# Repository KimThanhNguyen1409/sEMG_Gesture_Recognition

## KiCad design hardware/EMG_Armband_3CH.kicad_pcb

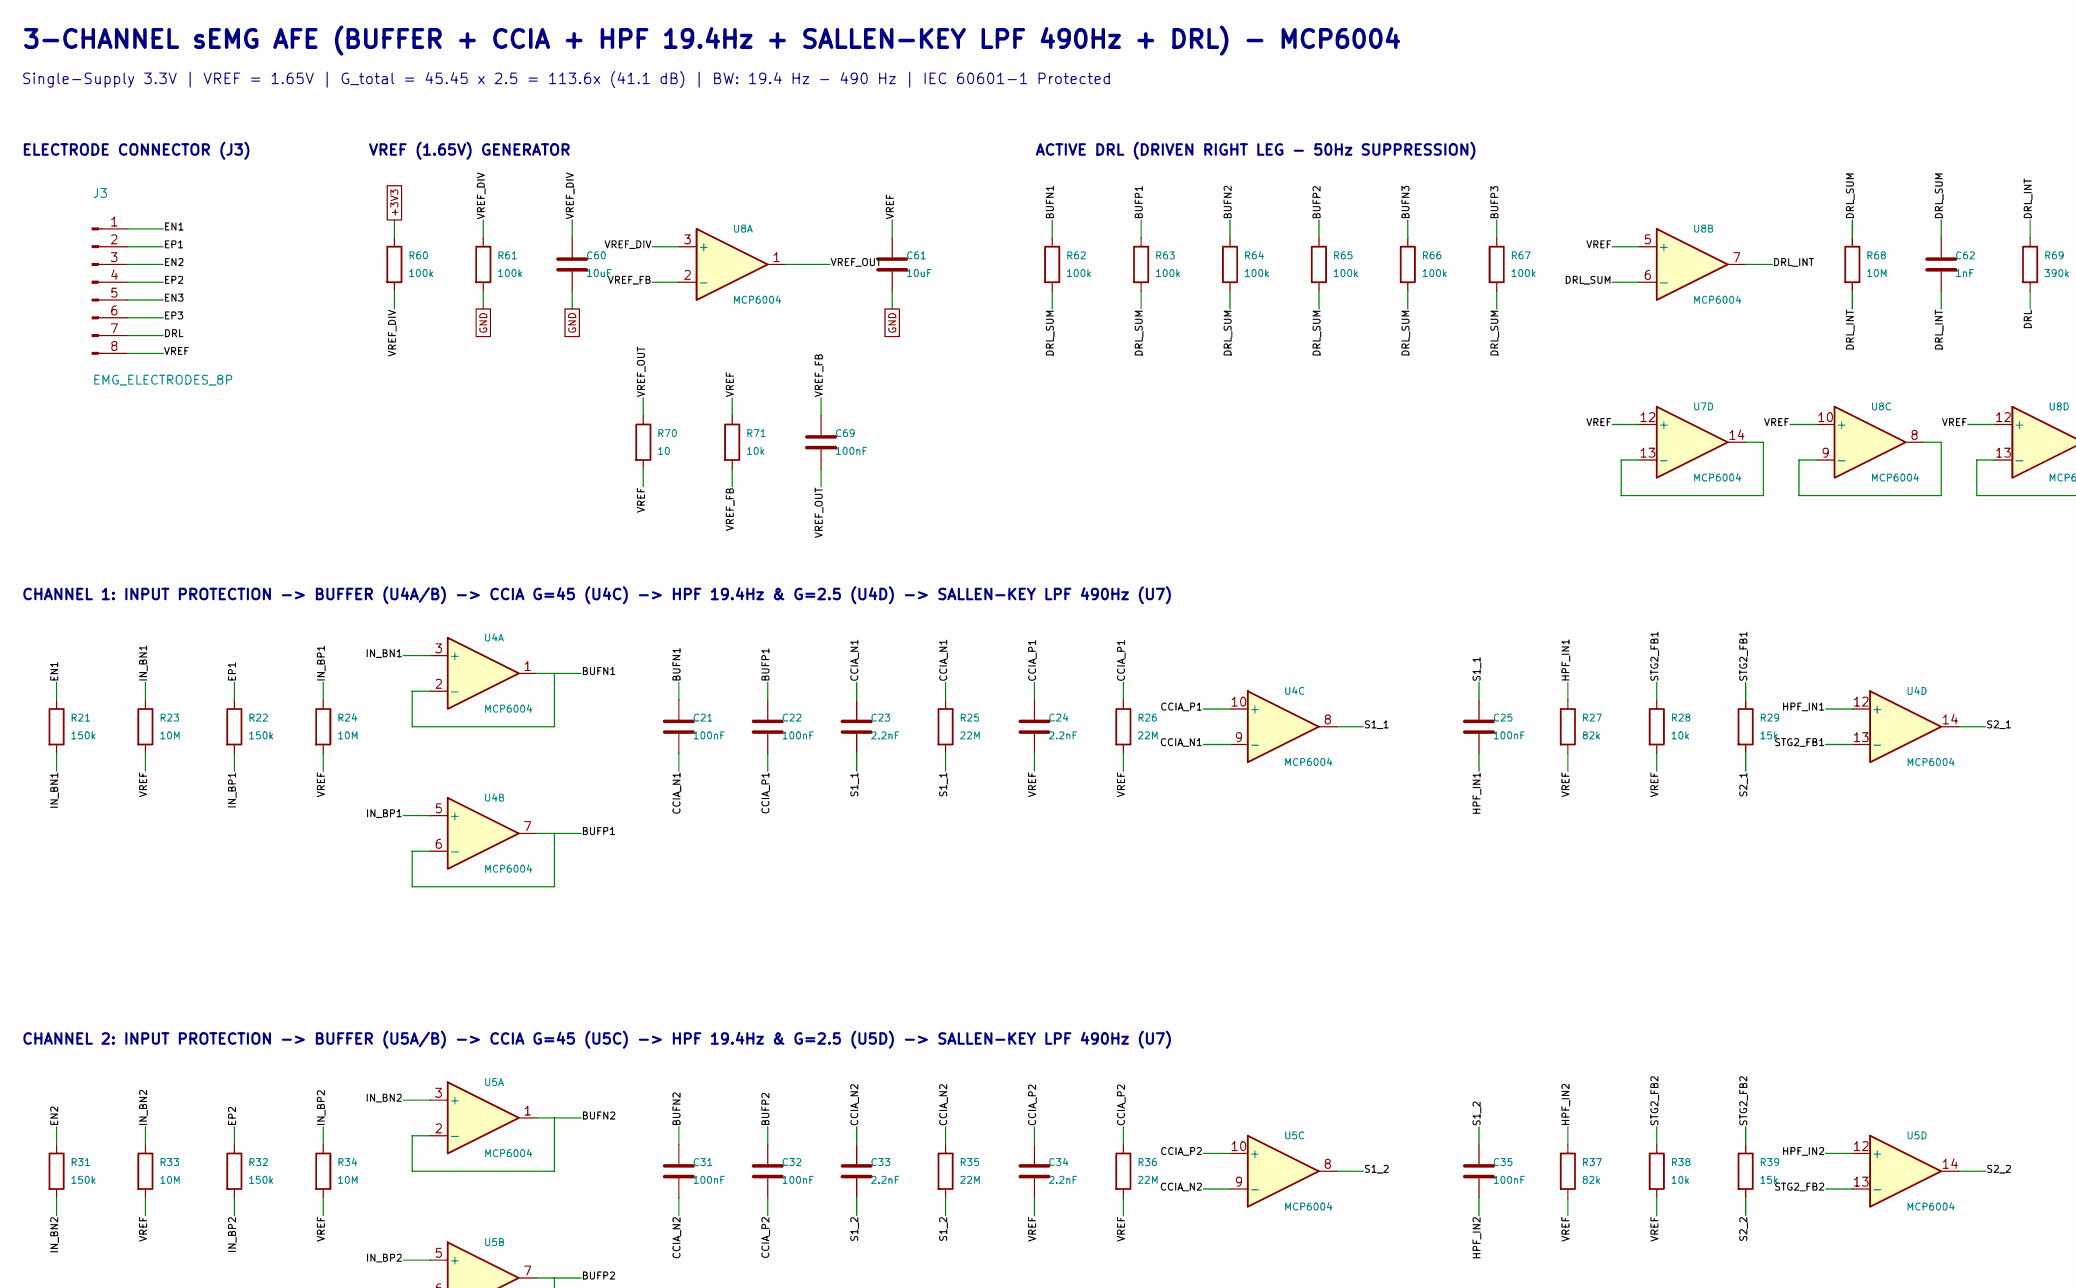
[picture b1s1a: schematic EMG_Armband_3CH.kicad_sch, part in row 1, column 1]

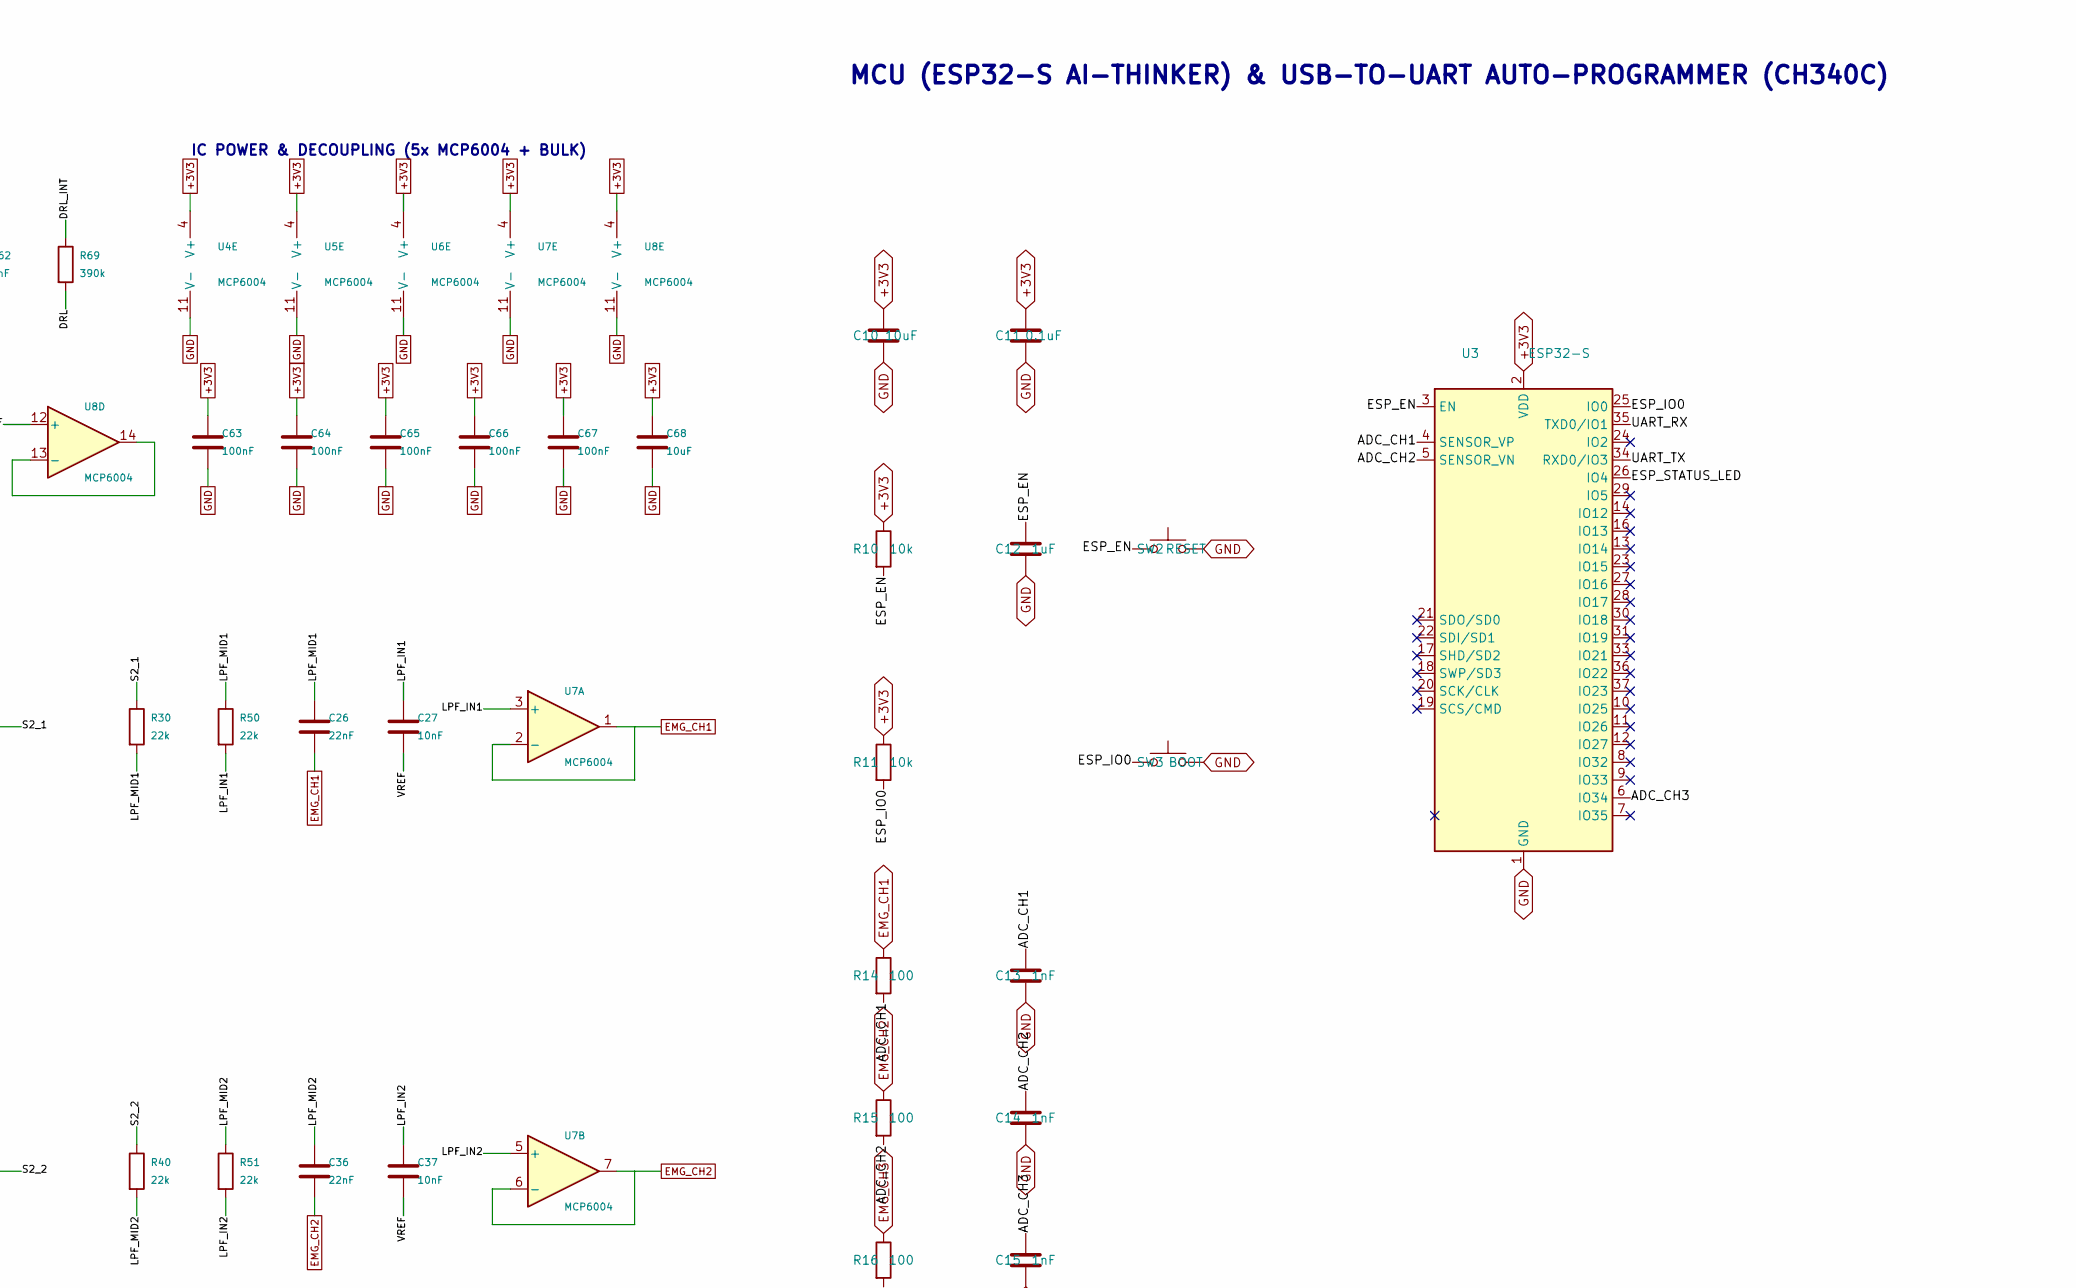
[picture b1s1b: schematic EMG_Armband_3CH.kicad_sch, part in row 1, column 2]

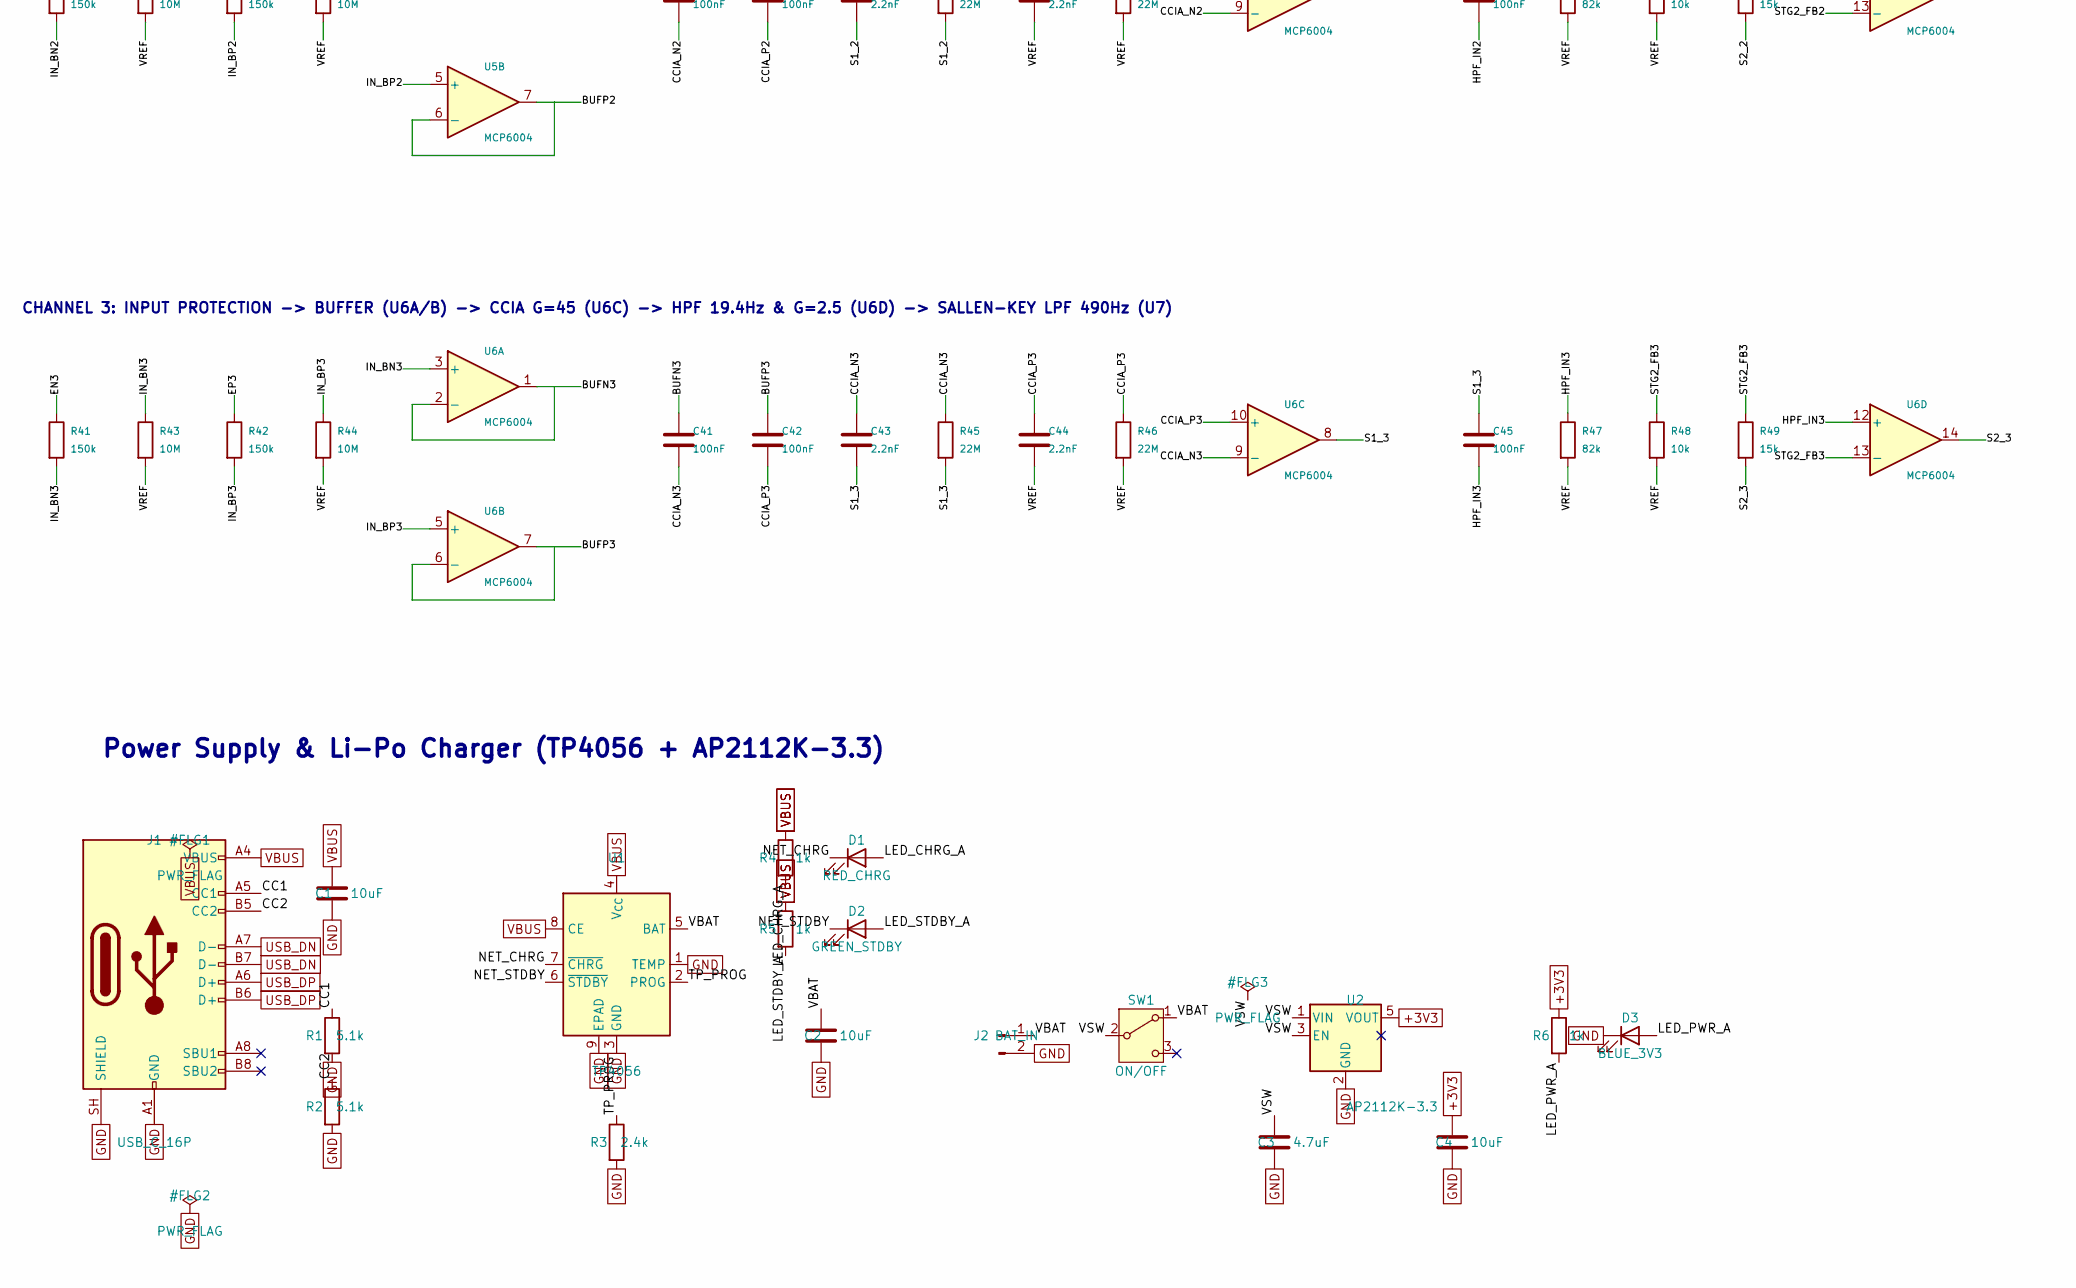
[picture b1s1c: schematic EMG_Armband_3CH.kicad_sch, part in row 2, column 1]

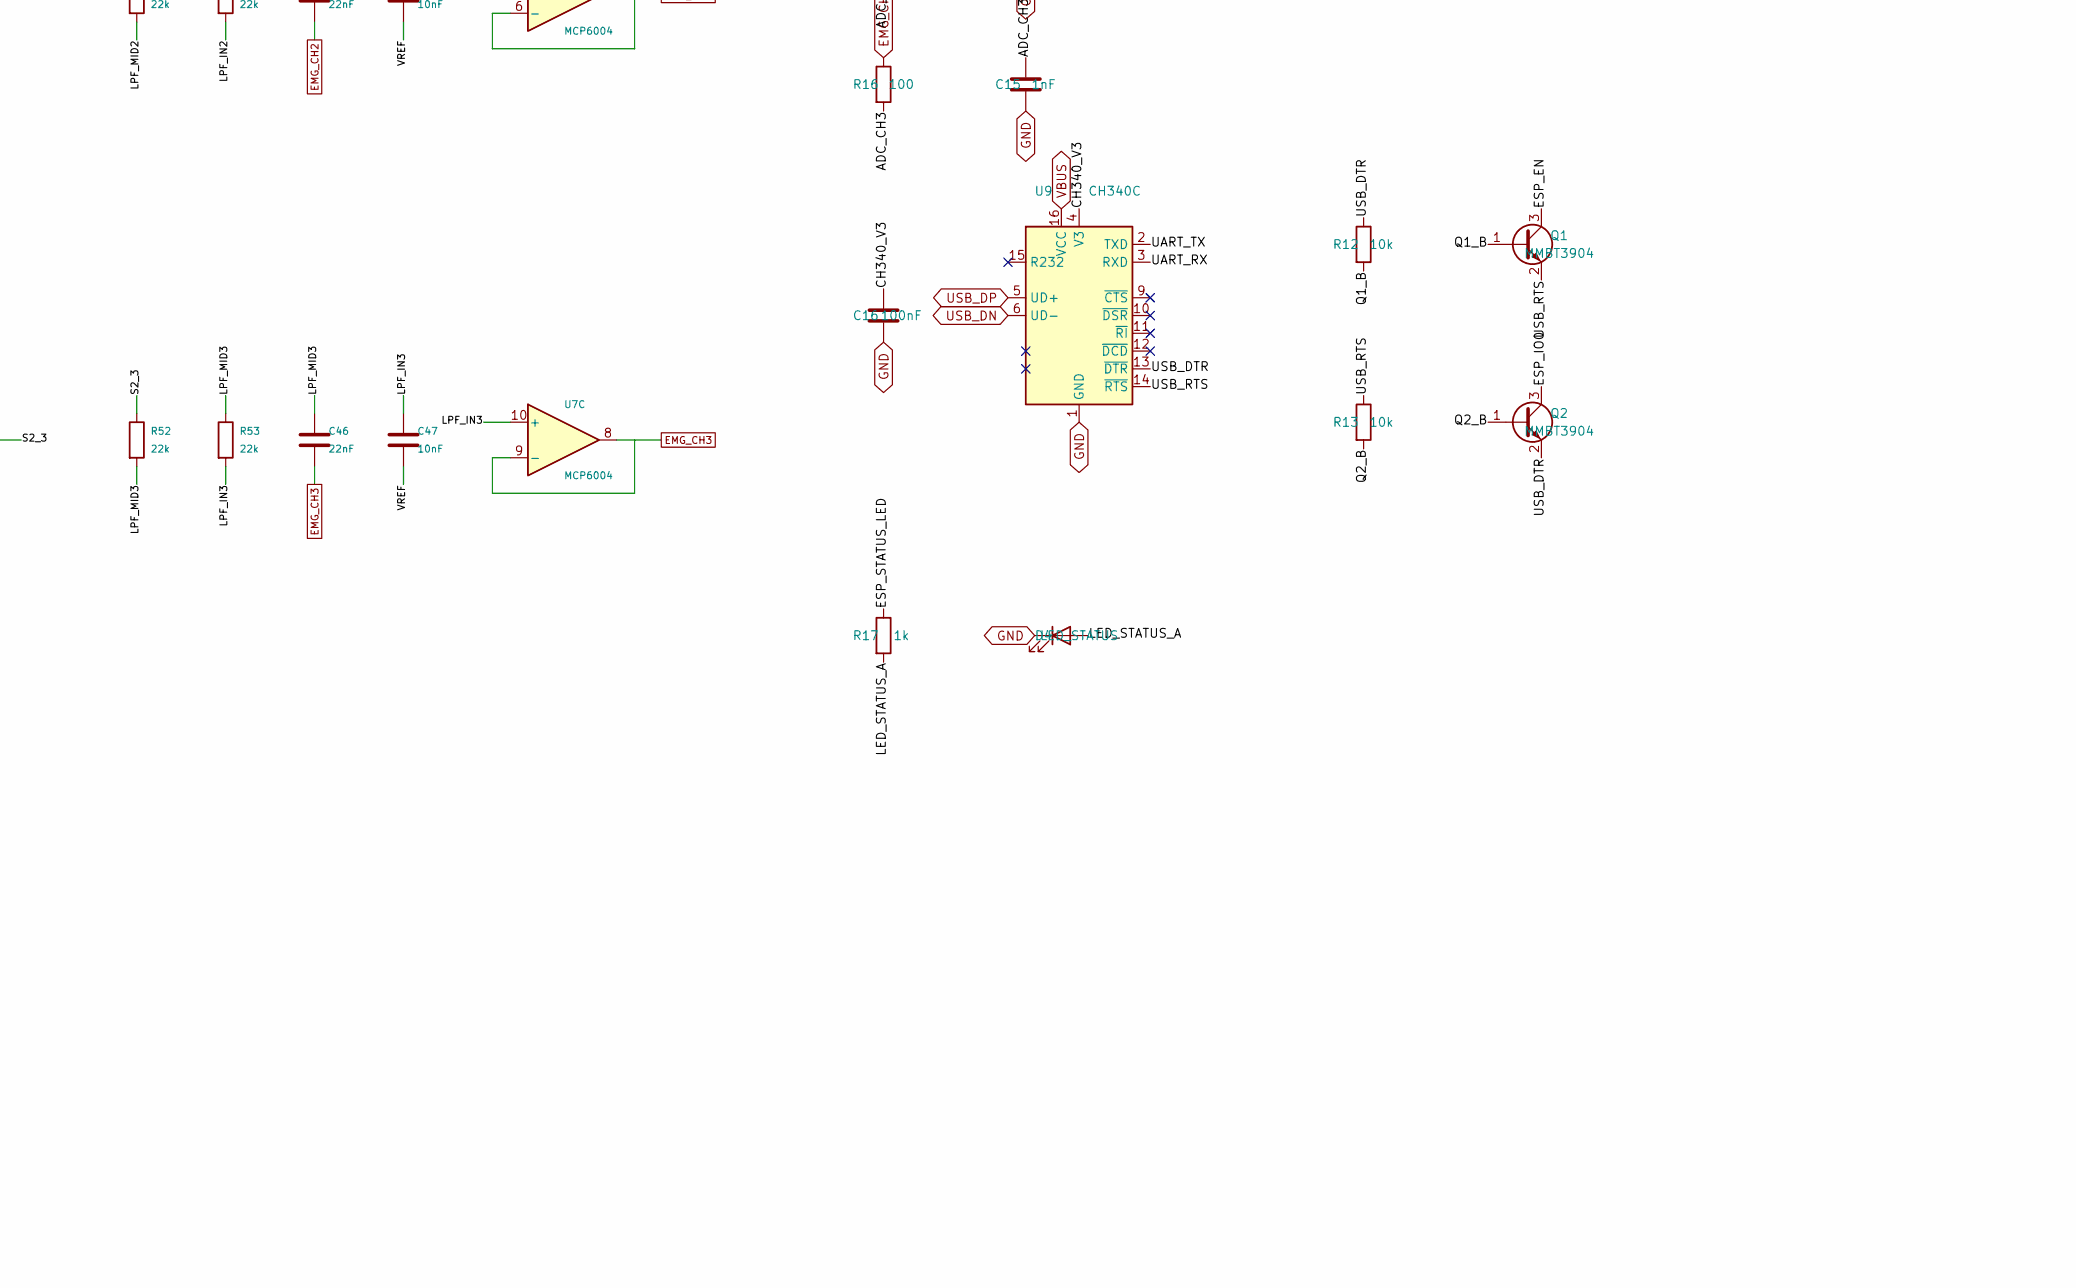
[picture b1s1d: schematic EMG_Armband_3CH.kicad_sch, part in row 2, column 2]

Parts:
C1, C2, C4, C10, C60, C61, C68: 10uF; C_0805_2012Metric
C3: 4.7uF; C_0805_2012Metric
C11: 0.1uF; C_0805_2012Metric
C12: 1uF; C_0805_2012Metric
C13, C14, C15, C62: 1nF; C_0805_2012Metric
C16, C25, C35, C45, C63, C64, C65, C66, C67, C69: 100nF; C_0805_2012Metric
C21, C22, C31, C32, C41, C42: 100nF; C_1206_3216Metric
C23, C24, C33, C34, C43, C44: 2.2nF; C_0805_2012Metric
C26, C36, C46: 22nF; C_0805_2012Metric
C27, C37, C47: 10nF; C_0805_2012Metric
D1: RED_CHRG; LED_0805_2012Metric
D2: GREEN_STDBY; LED_0805_2012Metric
D3: BLUE_3V3; LED_0805_2012Metric
D4: LED_STATUS; LED_0805_2012Metric
J1: USB_C_16P; USB_C_Receptacle_HRO_TYPE-C-31-M-12
J2: BAT_IN; JST_PH_B2B-PH-K_1x02_P2.00mm_Vertical
J3: EMG_ELECTRODES_8P; PinHeader_1x08_P2.54mm_Vertical
Q1, Q2: MMBT3904; SOT-23
R1, R2: 5.1k; R_0805_2012Metric
R3: 2.4k; R_0805_2012Metric
R4, R5, R6, R17: 1k; R_0805_2012Metric
R10, R11, R12, R13, R28, R38, R48, R71: 10k; R_0805_2012Metric
R14, R15, R16: 100; R_0805_2012Metric
R21, R22, R31, R32, R41, R42: 150k; R_0805_2012Metric
R23, R24, R33, R34, R43, R44, R68: 10M; R_0805_2012Metric
R25, R26, R35, R36, R45, R46: 22M; R_0805_2012Metric
R27, R37, R47: 82k; R_0805_2012Metric
R29, R39, R49: 15k; R_0805_2012Metric
R30, R40, R50, R51, R52, R53: 22k; R_0805_2012Metric
R60, R61, R62, R63, R64, R65, R66, R67: 100k; R_0805_2012Metric
R69: 390k; R_0805_2012Metric
R70: 10; R_0805_2012Metric
SW1: ON/OFF; SW_SPDT_PCM12
SW2: RESET; SW_Push_SPST_NO_Alps_SKRK
SW3: BOOT; SW_Push_SPST_NO_Alps_SKRK
U1: TP4056; SOIC-8-1EP_3.9x4.9mm_P1.27mm_EP2.41x3.3mm
U2: AP2112K-3.3; SOT-23-5
U3: ESP32-S; ESP32-WROOM-32
U4, U5, U6, U7, U8: MCP6004; SOIC-14_3.9x8.7mm_P1.27mm
U9: CH340C; SOIC-16_3.9x9.9mm_P1.27mm

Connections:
+3V3: C4.1, C10.1, C11.1, C63.1, C64.1, C65.1, C66.1, C67.1, C68.1, R6.1, R10.1, R11.1, R60.1, U2.5 (VOUT), U3.2 (VDD), U4.4 (V+), U5.4 (V+), U6.4 (V+), U7.4 (V+), U8.4 (V+)
/ADC_CH1: C13.1, R14.2, U3.4 (SENSOR_VP)
/ADC_CH2: C14.1, R15.2, U3.5 (SENSOR_VN)
/ADC_CH3: C15.1, R16.2, U3.6 (IO34)
/BUFN1: C21.1, R62.1, U4.1, U4.2 (-)
/BUFN2: C31.1, R64.1, U5.1, U5.2 (-)
/BUFN3: C41.1, R66.1, U6.1, U6.2 (-)
/BUFP1: C22.1, R63.1, U4.6 (-), U4.7
/BUFP2: C32.1, R65.1, U5.6 (-), U5.7
/BUFP3: C42.1, R67.1, U6.6 (-), U6.7
/CC1: J1.A5 (CC1), R1.1
/CC2: J1.B5 (CC2), R2.1
/CCIA_N1: C21.2, C23.1, R25.1, U4.9 (-)
/CCIA_N2: C31.2, C33.1, R35.1, U5.9 (-)
/CCIA_N3: C41.2, C43.1, R45.1, U6.9 (-)
/CCIA_P1: C22.2, C24.1, R26.1, U4.10 (+)
/CCIA_P2: C32.2, C34.1, R36.1, U5.10 (+)
/CCIA_P3: C42.2, C44.1, R46.1, U6.10 (+)
/CH340_V3: C16.1, U9.4 (V3)
/DRL: J3.7, R69.2
/DRL_INT: C62.2, R68.2, R69.1, U8.7
/DRL_SUM: C62.1, R62.2, R63.2, R64.2, R65.2, R66.2, R67.2, R68.1, U8.6 (-)
/EN1: J3.1, R21.1
/EN2: J3.3, R31.1
/EN3: J3.5, R41.1
/EP1: J3.2, R22.1
/EP2: J3.4, R32.1
/EP3: J3.6, R42.1
/ESP_EN: C12.1, Q1.3 (C), R10.2, SW2.1, U3.3 (EN)
/ESP_IO0: Q2.3 (C), R11.2, SW3.1, U3.25 (IO0)
/ESP_STATUS_LED: R17.1, U3.26 (IO4)
/HPF_IN1: C25.2, R27.1, U4.12 (+)
/HPF_IN2: C35.2, R37.1, U5.12 (+)
/HPF_IN3: C45.2, R47.1, U6.12 (+)
/IN_BN1: R21.2, R23.1, U4.3 (+)
/IN_BN2: R31.2, R33.1, U5.3 (+)
/IN_BN3: R41.2, R43.1, U6.3 (+)
/IN_BP1: R22.2, R24.1, U4.5 (+)
/IN_BP2: R32.2, R34.1, U5.5 (+)
/IN_BP3: R42.2, R44.1, U6.5 (+)
/LED_CHRG_A: D1.2 (A), R4.2
/LED_PWR_A: D3.2 (A), R6.2
/LED_STATUS_A: D4.2 (A), R17.2
/LED_STDBY_A: D2.2 (A), R5.2
/LPF_IN1: C27.1, R50.2, U7.3 (+)
/LPF_IN2: C37.1, R51.2, U7.5 (+)
/LPF_IN3: C47.1, R53.2, U7.10 (+)
/LPF_MID1: C26.1, R30.2, R50.1
/LPF_MID2: C36.1, R40.2, R51.1
/LPF_MID3: C46.1, R52.2, R53.1
/NET_CHRG: D1.1 (K), U1.7 (~CHRG)
/NET_STDBY: D2.1 (K), U1.6 (~STDBY)
/Q1_B: Q1.1 (B), R12.2
/Q2_B: Q2.1 (B), R13.2
/S1_1: C23.2, C25.1, R25.2, U4.8
/S1_2: C33.2, C35.1, R35.2, U5.8
/S1_3: C43.2, C45.1, R45.2, U6.8
/S2_1: R29.2, R30.1, U4.14
/S2_2: R39.2, R40.1, U5.14
/S2_3: R49.2, R52.1, U6.14
/STG2_FB1: R28.1, R29.1, U4.13 (-)
/STG2_FB2: R38.1, R39.1, U5.13 (-)
/STG2_FB3: R48.1, R49.1, U6.13 (-)
/TP_PROG: R3.1, U1.2 (PROG)
/UART_RX: U3.35 (TXD0/IO1), U9.3 (RXD)
/UART_TX: U3.34 (RXD0/IO3), U9.2 (TXD)
/USB_DTR: Q2.2 (E), R12.1, U9.13 (~DTR)
/USB_RTS: Q1.2 (E), R13.1, U9.14 (~RTS)
/VBAT: C2.1, J2.1, SW1.1 (A), U1.5 (BAT)
/VREF: C24.2, C27.2, C34.2, C37.2, C44.2, C47.2, C61.1, J3.8, R23.2, R24.2, R26.2, R27.2, R28.2, R33.2, R34.2, R36.2, R37.2, R38.2, R43.2, R44.2, R46.2, R47.2, R48.2, R70.2, R71.1, U7.12 (+), U8.5 (+), U8.10 (+), U8.12 (+)
/VREF_DIV: C60.1, R60.2, R61.1, U8.3 (+)
/VREF_FB: C69.1, R71.2, U8.2 (-)
/VREF_OUT: C69.2, R70.1, U8.1
/VSW: C3.1, SW1.2 (B), U2.1 (VIN), U2.3 (EN)
EMG_CH1: C26.2, R14.1, U7.1, U7.2 (-)
EMG_CH2: C36.2, R15.1, U7.6 (-), U7.7
EMG_CH3: C46.2, R16.1, U7.8, U7.9 (-)
GND: C1.2, C2.2, C3.2, C4.2, C10.2, C11.2, C12.2, C13.2, C14.2, C15.2, C16.2, C60.2, C61.2, C63.2, C64.2, C65.2, C66.2, C67.2, C68.2, D3.1 (K), D4.1 (K), J1.A1 (GND), J1.A12 (GND), J1.B1 (GND), J1.B12 (GND), J1.SH (SHIELD), J2.2, R1.2, R2.2, R3.2, R61.2, SW2.2, SW3.2, U1.1 (TEMP), U1.3 (GND), U1.9 (EPAD), U2.2 (GND), U3.1 (GND), U3.15 (GND), U3.38 (GND), U3.39 (GND), U4.11 (V-), U5.11 (V-), U6.11 (V-), U7.11 (V-), U8.11 (V-), U9.1 (GND)
unnamed: U7.13 (-), U7.14
unnamed: U8.8, U8.9 (-)
unnamed: U8.13 (-), U8.14
USB_DN: J1.A7 (D-), J1.B7 (D-), U9.6 (UD-)
USB_DP: J1.A6 (D+), J1.B6 (D+), U9.5 (UD+)
VBUS: C1.1, J1.A4 (VBUS), J1.A9 (VBUS), J1.B4 (VBUS), J1.B9 (VBUS), R4.1, R5.1, U1.4 (V_{CC}), U1.8 (CE), U9.16 (VCC)

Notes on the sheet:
3-CHANNEL sEMG AFE (BUFFER + CCIA + HPF 19.4Hz + SALLEN-KEY LPF 490Hz + DRL) - MCP6004
Single-Supply 3.3V | VREF = 1.65V | G_total = 45.45 x 2.5 = 113.6x (41.1 dB) | BW: 19.4 Hz - 490 Hz | IEC 60601-1 Protected
ELECTRODE CONNECTOR (J3)
VREF (1.65V) GENERATOR
ACTIVE DRL (DRIVEN RIGHT LEG - 50Hz SUPPRESSION)
IC POWER & DECOUPLING (5x MCP6004 + BULK)
CHANNEL 1: INPUT PROTECTION -> BUFFER (U4A/B) -> CCIA G=45 (U4C) -> HPF 19.4Hz & G=2.5 (U4D) -> SALLEN-KEY LPF 490Hz (U7)
CHANNEL 2: INPUT PROTECTION -> BUFFER (U5A/B) -> CCIA G=45 (U5C) -> HPF 19.4Hz & G=2.5 (U5D) -> SALLEN-KEY LPF 490Hz (U7)
CHANNEL 3: INPUT PROTECTION -> BUFFER (U6A/B) -> CCIA G=45 (U6C) -> HPF 19.4Hz & G=2.5 (U6D) -> SALLEN-KEY LPF 490Hz (U7)
MCU (ESP32-S AI-THINKER) & USB-TO-UART AUTO-PROGRAMMER (CH340C)
Power Supply & Li-Po Charger (TP4056 + AP2112K-3.3)

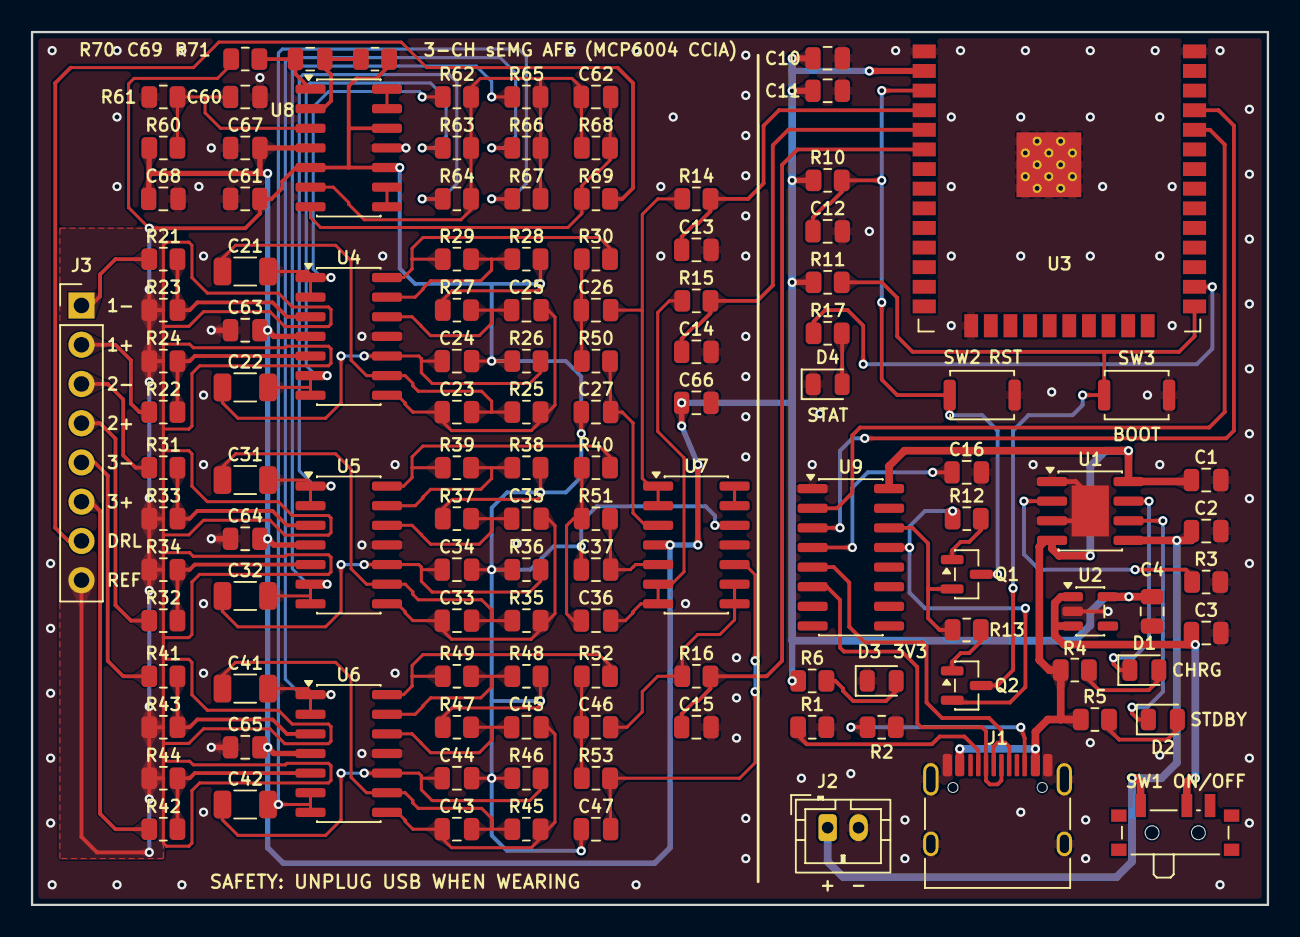
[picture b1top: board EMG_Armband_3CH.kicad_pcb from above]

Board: 2 copper layers, 80.0 x 56.5 mm, 122 parts (0 on the bottom side), 84 nets.

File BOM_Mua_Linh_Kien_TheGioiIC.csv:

STT,Nhóm,Mã hiển thị (Ref),Tên linh kiện / Trị số,Đóng gói (Footprint),Số lượng mạch cần,Số lượng nên mua,Đơn giá tham khảo (VNĐ/cái),Thành tiền dự tính (VNĐ),Từ khóa tìm kiếm trên Thegioiic.com,Ghi chú kỹ thuật khi chọn mua
1,IC,U4 U5 U6 U7 U8,MCP6004-I/SL,SOIC-14 (SOP-14),5,6,8000,48000,MCP6004-I/SL hoặc MCP6004 SOP14,IC Op-Amp Quad 4 kênh Rail-to-Rail. Mua gói SOP-14 chân dán. (Nếu Thegioiic hết hàng thì Shopee bán vỉ 5 con ~35-50k).
2,IC,U3,ESP32-S Ai-Thinker,SMD-38 (ESP32-WROOM-32),1,1,115140,115140,ESP32-S Ai-Thinker (Mã IC38424),Module WiFi + Bluetooth SMD-38 của Ai-Thinker (38 chân dán + 1 chân GND bụng).
3,IC,U9,CH340C,SOIC-16 (SOP-16),1,2,14820,29640,CH340C SOP-16 (Mã IC36480),IC chuyển đổi USB sang UART có sẵn dao động nội 12MHz (không cần thạch anh rời).
4,IC,U1,TP4056,SOP-8-EP (ESOP-8),1,2,5700,11400,TP4056 SOP8,IC sạc pin Li-Po 1A. Chọn loại chân dán SOP-8 có pad tản nhiệt dưới bụng.
5,IC,U2,AP2112K-3.3,SOT-23-5,1,2,4500,9000,AP2112K-3.3 hoặc SOT-23-5 3.3V,LDO 3.3V 600mA cực thấp ồn. (Có thể thay bằng RT9193-33GB hoặc ME6211C33M5G cùng chân SOT-23-5).
6,Transistor,Q1 Q2,MMBT3904 (hoặc S8050 / BC817),SOT-23,2,5,300,1500,MMBT3904 SOT-23 hoặc BC817 SOT-23,Transistor NPN dán SOT-23 (Chân 1=B, 2=E, 3=C) cho mạch tự động nạp code DTR/RTS.
7,Tụ điện,C21 C22 C31 C32 C41 C42,100nF (0.1uF / 104),SMD 1206,6,10,1200,12000,Tụ 1206 100nF hoặc Tụ 1206 0.1uF,QUAN TRỌNG: 6 tụ đầu vào CCIA. Ưu tiên chọn loại gốm C0G / NP0 sai số 5% hoặc 1% (chịu áp >= 25V) để giữ CMRR cân bằng.
8,Tụ điện,C23 C24 C33 C34 C43 C44,2.2nF (mã 222),SMD 0805,6,10,350,3500,Tụ 0805 2.2nF hoặc Tụ 0805 222,Tụ hồi tiếp CCIA (G=45.45x). Ưu tiên C0G/NP0 hoặc X7R.
9,Tụ điện,C11 C16 C25 C35 C45 C63 C64 C65 C66 C67,100nF (0.1uF / 104),SMD 0805,10,20,250,5000,Tụ 0805 100nF hoặc Tụ 0805 0.1uF,Tụ lọc HPF 19.4Hz, tụ lọc V3 của CH340C và các tụ bypass nguồn 3.3V.
10,Tụ điện,C26 C36 C46,22nF (mã 223),SMD 0805,3,10,350,3500,Tụ 0805 22nF hoặc Tụ 0805 223,Tụ lọc thông thấp Sallen-Key Butterworth 490Hz (C1).
11,Tụ điện,C27 C37 C47,10nF (mã 103),SMD 0805,3,10,300,3000,Tụ 0805 10nF hoặc Tụ 0805 103,Tụ lọc thông thấp Sallen-Key Butterworth 490Hz (C2).
12,Tụ điện,C13 C14 C15 C62,1nF (mã 102),SMD 0805,4,10,300,3000,Tụ 0805 1nF hoặc Tụ 0805 102,Tụ tích phân DRL (C62) và 3 tụ lọc RC trước ngõ vào ADC1 của ESP32-S.
13,Tụ điện,C1 C2 C4 C10 C60 C61 C68,10uF (mã 106),SMD 0805,7,15,650,9750,Tụ 0805 10uF,Tụ lọc nguồn VBUS, VBAT, +3V3 và lọc ổn định áp chuẩn VREF = 1.65V. Chọn tụ MLCC chịu áp >= 10V (10V/16V/25V).
14,Tụ điện,C3,4.7uF,SMD 0805,1,5,550,2750,Tụ 0805 4.7uF,Tụ ngõ vào LDO AP2112K.
15,Tụ điện,C12,1uF (mã 105),SMD 0805,1,5,400,2000,Tụ 0805 1uF,Tụ định thì trễ chân EN (Reset) cho ESP32-S.
16,Điện trở,R21 R22 R31 R32 R41 R42,150kΩ (mã 154),SMD 0805,6,10,150,1500,Trở 0805 150k,Trở bảo vệ ngõ vào điện cực người dùng đạt chuẩn an toàn y tế IEC 60601-1 (giới hạn dòng rò < 25uA).
17,Điện trở,R23 R24 R33 R34 R43 R44 R68,10MΩ (mã 106),SMD 0805,7,10,250,2500,Trở 0805 10M,Trở phân cực ngõ vào Buffer về VREF và trở hồi tiếp DC mạch DRL.
18,Điện trở,R25 R26 R35 R36 R45 R46,22MΩ (mã 226),SMD 0805,6,10,300,3000,Trở 0805 22M,Trở hồi tiếp DC tầng CCIA định hình tần số cắt dưới 3.3Hz.
19,Điện trở,R27 R37 R47,82kΩ (mã 823),SMD 0805,3,10,150,1500,Trở 0805 82k,Trở định tần số cắt tầng lọc thông cao HPF 19.4Hz.
20,Điện trở,R29 R39 R49,15kΩ (mã 153),SMD 0805,3,10,150,1500,Trở 0805 15k,Trở hồi tiếp RF tầng HPF (độ lợi G = 2.5x).
21,Điện trở,R10 R11 R12 R13 R28 R38 R48,10kΩ (mã 103),SMD 0805,7,20,100,2000,Trở 0805 10k,Trở RG tầng HPF, trở pull-up EN/IO0 và trở cực Base của Q1/Q2 mạch Auto-Reset.
22,Điện trở,R30 R40 R50 R51 R52 R53,22kΩ (mã 223),SMD 0805,6,10,150,1500,Trở 0805 22k,Cặp trở R1 R2 cho mạch lọc thông thấp tích cực Sallen-Key 490Hz.
23,Điện trở,R60 R61 R62 R63 R64 R65 R66 R67,100kΩ (mã 104),SMD 0805,8,20,100,2000,Trở 0805 100k,Cầu chia áp VREF 1.65V và 6 trở lấy trung bình sai số chế độ chung vào mạch DRL.
24,Điện trở,R69,390kΩ (mã 394),SMD 0805,1,5,150,750,Trở 0805 390k,Trở an toàn bảo vệ ngõ ra DRL nối về cơ thể người.
25,Điện trở,R1 R2,5.1kΩ (mã 512),SMD 0805,2,10,150,1500,Trở 0805 5.1k,Trở kéo CC1 CC2 cổng Type-C nhận diện nguồn cấp sạc 5V.
26,Điện trở,R3,2.4kΩ (mã 242),SMD 0805,1,5,150,750,Trở 0805 2.4k,Trở cấu hình dòng sạc TP4056 (xấp xỉ 500mA an toàn cho pin Li-Po 500-1000mAh).
27,Điện trở,R4 R5 R6 R17,1kΩ (mã 102),SMD 0805,4,20,100,2000,Trở 0805 1k,Trở hạn dòng cho các đèn LED báo nguồn sạc và trạng thái.
28,Điện trở,R14 R15 R16,100Ω (mã 101),SMD 0805,3,10,150,1500,Trở 0805 100R,Trở lọc RC trước chân ADC1 (GPIO36, GPIO39, GPIO34) của ESP32-S.
29,LED,D1,Đỏ (RED),LED 0805 SMD,1,5,300,1500,LED 0805 Đỏ,LED báo trạng thái sạc pin (CHRG).
30,LED,D2,Xanh lá (GREEN),LED 0805 SMD,1,5,350,1750,LED 0805 Xanh lá,LED báo sạc đầy pin (STDBY).
31,LED,D3,Xanh dương (BLUE),LED 0805 SMD,1,5,400,2000,LED 0805 Xanh dương,LED báo nguồn hệ thống 3.3V (PWR).
32,LED,D4,Vàng hoặc Xanh,LED 0805 SMD,1,5,350,1750,LED 0805 Vàng / Xanh,LED chỉ báo trạng thái chương trình nối chân IO4 ESP32-S.
33,Đầu nối,J1,USB Type-C 16 chân,TYPE-C-31-M-12 SMD,1,2,1800,3600,Cổng USB Type C 16 chân SMD,Cổng sạc và nạp code qua CH340C cho ESP32-S. Chân dán SMD có 4 chấu định vị xuyên lỗ.
34,Đầu nối,J2,JST-PH 2-pin đực thẳng,JST-PH-2P 2.0mm Vertical,1,2,300,600,Jack JST PH2.0 2P đực thẳng,Đầu cắm giắc pin Li-Po 3.7V tiêu chuẩn (khoảng cách chân 2.0mm).
35,Đầu nối,J3,Header 1x8P 2.54mm đực thẳng,PinHeader 1x08 P=2.54mm,1,1 thanh,2500,2500,Hàng rào đực 1x40 2.54mm,Hàng rào cắm dây ra 3 cặp điện cực đo và cực DRL VREF.
36,Nút nhấn,SW2 SW3,Nút nhấn SMD 2 chân,SW_Push SMD (Alps SKRK 3.9x2.9mm),2,5,800,4000,Nút nhấn SMD 2 chân 3x4 hoặc 3x6,Nút bấm Reset (EN) và nút Boot (IO0).
37,Công tắc,SW1,Công tắc gạt trượt SMD 3 chân,SW_SPDT_PCM12,1,2,1500,3000,Công tắc gạt SMD 3 chân hoặc PCM12,Công tắc nguồn On/Off từ pin sang mạch.
38,Phụ kiện,Điện cực,Miếng dán điện cực tim/cơ y tế ECG/EMG (nút Snap),Điện cực dán y tế dùng 1 lần (bịch 50 cái),7,1 bịch (50 cái),50000,50000,Điện cực dán nút bấm Snap 3M / Contec hoặc Miếng dán điện cực tim,Bịch 50 miếng dán có sẵn gel dẫn điện (dùng 2 miếng/kênh x 3 kênh + 1 miếng DRL tham chiếu).
39,Phụ kiện,Cáp nối,Bộ dây cáp kẹp điện cực nút bấm (Snap to Dupont / Jack 3.5),Dây cáp y tế chuyên dụng (bộ 10 sợi),7,1 bộ (10 sợi),70000,70000,Dây dẫn điện cực ECG Snap to Dupont hoặc Dây điện cực nút bấm 3.5mm,Dây nối từ các nút dán trên bắp tay về trạm cắm Header J3 trên bo mạch.
,,,TỔNG CHI PHÍ LINH KIỆN DỰ TÍNH (ĐÃ BAO GỒM DỰ PHÒNG & PHỤ KIỆN ĐO),,,,,418680,,Ước tính khoảng 418.000 VNĐ cho toàn bộ 119 linh kiện bo mạch + bịch 50 điện cực dán và bộ 10 dây cáp kẹp.

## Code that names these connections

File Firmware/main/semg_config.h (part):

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#else
/* Custom PCB layout / Mock channels: Pads 4, 5, 6 -> GPIO 36, 39, 34 */
#define SEMG_CH1_GPIO                  (GPIO_NUM_36)
#define SEMG_CH1_ADC_CHANNEL           (ADC_CHANNEL_0) /* SENSOR_VP (Pad 4) -> ADC_CH1 */

#define SEMG_CH2_GPIO                  (GPIO_NUM_39)
#define SEMG_CH2_ADC_CHANNEL           (ADC_CHANNEL_3) /* SENSOR_VN (Pad 5) -> ADC_CH2 */

#define SEMG_CH3_GPIO                  (GPIO_NUM_34)
#define SEMG_CH3_ADC_CHANNEL           (ADC_CHANNEL_6) /* IO34      (Pad 6) -> ADC_CH3 */
#endif

#define SEMG_ADC_ATTEN                 (ADC_ATTEN_DB_12)
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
